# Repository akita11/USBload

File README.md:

# USBload
Dummy USB load

## これは何？
マイコンボードやLEDなどをモバイルバッテリーで駆動させるとき、急に電源が切れてしまうことはありませんか？
大抵のモバイルバッテリーは消費電流が弱い時にスリープするようになっています。

本モジュールをモバイルバッテリーに取り付けることで、定期的に負荷電流を流すことで、モバイルバッテリーをスリープさせないようにすることができます。

本モジュールは間欠で電流を流すことで、モバイルバッテリーの動作時間により影響を与えないようにしました。
また、端子を結線することで、消費電流値と電流の間欠期間を設定できます。
それにより、使用するモバイルバッテリーの挙動に合わせ、動作を調整することができます。

## USBloadとUSBload2の違い
モバイルバッテリーによってオス側が差し込めないものがあるとのご意見を戴き、USBload2はAタイプのオスコネクタをつけました。

※USBload2.1では使用するマイコンがSTC8G1K08に変更になっていますが、使い方は変更ありません。

## 使い方
モバイルバッテリーに本モジュールのオス側を差し込み、メスコネクタに給電用USBケーブルを差し込むだけです。

※使用するモバイルバッテリーにあわせて、以下の「設定」を行う必要があります。

## 設定

### 電流間欠期間の設定方法

本モジュールを接続しない状態で、モバイルバッテリーをONにし、その後、自動的にスリープに入る（給電が止まる）までの時間を計測します。その時間に応じて、以下のとおり間欠期間を設定します。

間欠期間は、上記画像の赤色のA,Bパターンをショートすることで設定できます。

|A|B|間欠期間|補足|
|----|----|----|----|
|オープン|オープン|約24秒|30秒でスリープするモバイルバッテリー向け|
|ショート|オープン|約16秒|20秒でスリープするモバイルバッテリー向け|
|オープン|ショート|約12秒|15秒でスリープするモバイルバッテリー向け|
|ショート|ショート|約8秒|10秒でスリープするモバイルバッテリー向け|

### 消費電流値の設定方法
デフォルトで100mA流れるようになっており、上記画像の青色のパターンを1つショートするごとに電流値が100mA増えます。
多くのモバイルバッテリーは100mAのままでスリープを回避できるようですが、より多くの電流が必要なものもありますので、100mAのままではスリープを回避できない場合は、順に流す電流を増やしてください、

## その他
サイズ(USBload) : 18×12×10.5mm
サイズ(USBload2) : 35.6×17×11mm
モジュールの消費電流値 : 100mA～400mA  
モジュールの電流増減インターバル : 約10～30秒  

## （参考：自作する方向け）

USBload2.1（使用マイコン: STC8G1K08）のプログラムの書き込み方法はUSBload21_pgm.pdfを参照してください。

## 終わりに

USBloadの改良点がありましたら、ぜひIsuuesに書いてください。
こんな作品に作ったよ！という方は [#USBload](https://twitter.com/search?q=%23USBload&src=typed_query) を付けてSNSなどで公開してくださると嬉しいです。

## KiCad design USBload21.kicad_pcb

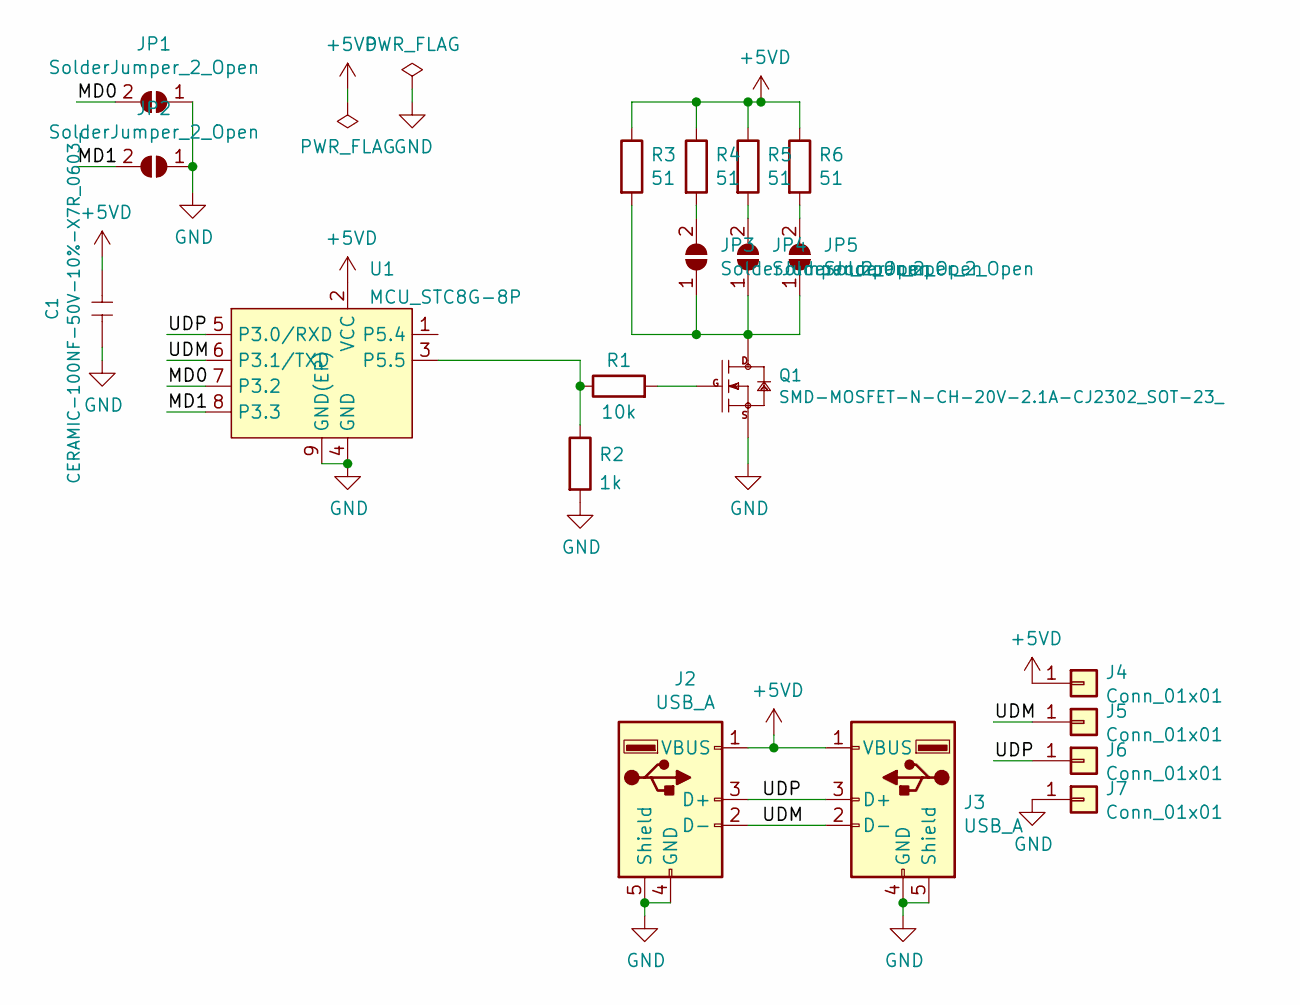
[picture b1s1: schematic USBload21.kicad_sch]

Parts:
C1: CERAMIC-100NF-50V-10%-X7R_0603_; C_0603_1608Metric; MPN CC0603KRX7R9BB104
J2: USB_A; USB-A_plug
J3: USB_A; USB_A_Stewart_SS-52100-001_Horizontal
J4, J5, J6, J7: Conn_01x01; Pad_SMD1.6mm
JP1, JP2, JP3, JP4, JP5: SolderJumper_2_Open; SolderJumper-2_P1.3mm_Open_RoundedPad1.0x1.5mm
Q1: SMD-MOSFET-N-CH-20V-2.1A-CJ2302_SOT-23_; SOT-23; MPN CJ2302
R1: 10k; R_0603_1608Metric
R2: 1k; R_0603_1608Metric
R3, R4, R5, R6: 51; R_0805_2012Metric
U1: MCU_STC8G-8P; DFN-8-1EP_3x3mm_P0.5mm_EP1.66x2.38mm

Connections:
+5VD: C1.2, J2.1 (VBUS), J3.1 (VBUS), J4.1, R3.1, R4.1, R5.1, R6.1, U1.2 (VCC)
/MD0: JP1.2 (B), U1.7 (P3.2)
/MD1: JP2.2 (B), U1.8 (P3.3)
/UDM: J2.2 (D-), J3.2 (D-), J5.1, U1.6 (P3.1/TXD)
/UDP: J2.3 (D+), J3.3 (D+), J6.1, U1.5 (P3.0/RXD)
GND: C1.1, J2.4 (GND), J2.5 (Shield), J3.4 (GND), J3.5 (Shield), J7.1, JP1.1 (A), JP2.1 (A), Q1.2 (S), R2.2, U1.4 (GND), U1.9 (GND(EP))
unnamed: JP3.1 (A), JP4.1 (A), JP5.1 (A), Q1.3 (D), R3.2
unnamed: JP3.2 (B), R4.2
unnamed: JP4.2 (B), R5.2
unnamed: JP5.2 (B), R6.2
unnamed: Q1.1 (G), R1.2
unnamed: R1.1, R2.1, U1.3 (P5.5)

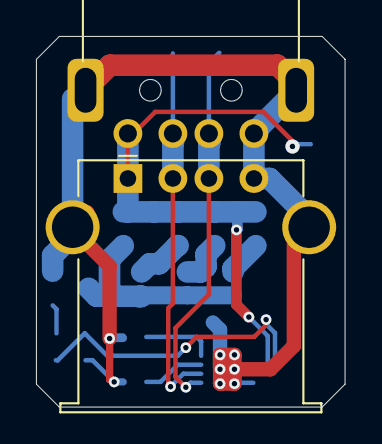
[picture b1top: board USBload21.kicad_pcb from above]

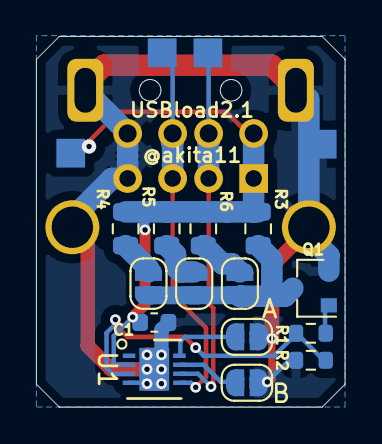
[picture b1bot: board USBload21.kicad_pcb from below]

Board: 2 copper layers, 17.1 x 20.6 mm, 20 parts (18 on the bottom side), 12 nets.

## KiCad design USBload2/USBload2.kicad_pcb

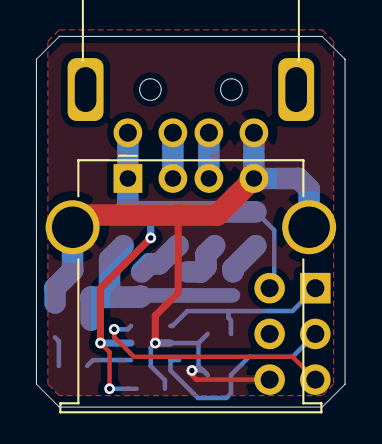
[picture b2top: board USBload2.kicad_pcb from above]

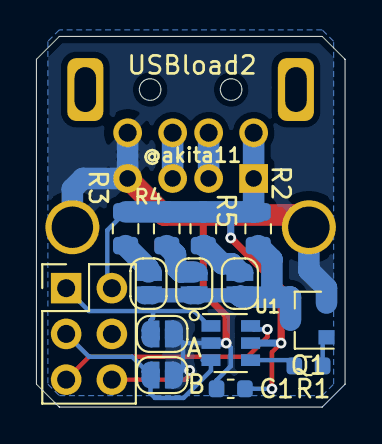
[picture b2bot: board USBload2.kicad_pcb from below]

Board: 2 copper layers, 17.1 x 20.6 mm, 16 parts (14 on the bottom side), 13 nets.

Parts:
C1: CERAMIC-100NF-50V-10%-X7R_0603_; C_0603_1608Metric
J1: AVR-ISP-6; PinHeader_2x03_P2.54mm_Vertical
J2: USB_A; USB-A_plug
J3: USB_A; USB_A_Stewart_SS-52100-001_Horizontal
JP1, JP2, JP3, JP4, JP5: SolderJumper_2_Open; SolderJumper-2_P1.3mm_Open_RoundedPad1.0x1.5mm
Q1: SMD-MOSFET-N-CH-20V-2.1A-CJ2302_SOT-23_; SOT-23
R1: SMD-RES-10K-1%-1_10W_0603_; R_0603_1608Metric
R2, R3, R4, R5: 51; R_0805_2012Metric
U1: ATtiny10-TS; SOT-23-6

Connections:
+5VD: C1.2, J1.2, J2.1, J3.1, R2.1, R3.1, R4.1, R5.1, U1.5
/PB0: J1.1, JP1.2, U1.1
/PB1: J1.3, JP2.2, U1.3
/PB3: J1.5, U1.6
GND: C1.1, J1.6, J2.4, J3.4, J3.5, JP1.1, JP2.1, Q1.2, U1.2
unnamed: J2.2, J3.2
unnamed: J2.3, J3.3
unnamed: JP3.1, JP4.1, JP5.1, Q1.3, R2.2
unnamed: JP3.2, R3.2
unnamed: JP4.2, R4.2
unnamed: JP5.2, R5.2
unnamed: Q1.1, R1.2
unnamed: R1.1, U1.4

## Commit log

2018-10-03 add PCB data
2018-10-03 add Arduino source
2018-10-09 Readmeの説明を追加
2018-10-09 設定方法を追記
2018-10-09 readmeを推敲
2020-07-08 USBload2に関する説明を追加
2021-05-15 ファイル名の整理とUSBload2のデータの追加
